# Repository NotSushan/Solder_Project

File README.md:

# CoolPCB

The main function of the PCB is that there is a button which will control the functioning of all the LEDs present in the board. 

## Schematic

## PCB

## How to build
Just order the PCB & components, open up the KiCAD file and build it accordingly.

## BOM
- 1 	Battery
- 4   LED
- 4	  470 Resistor
- 1 	Push Button

Made by Sushan!!

Made as a part of http://solder.hackclub.com/!

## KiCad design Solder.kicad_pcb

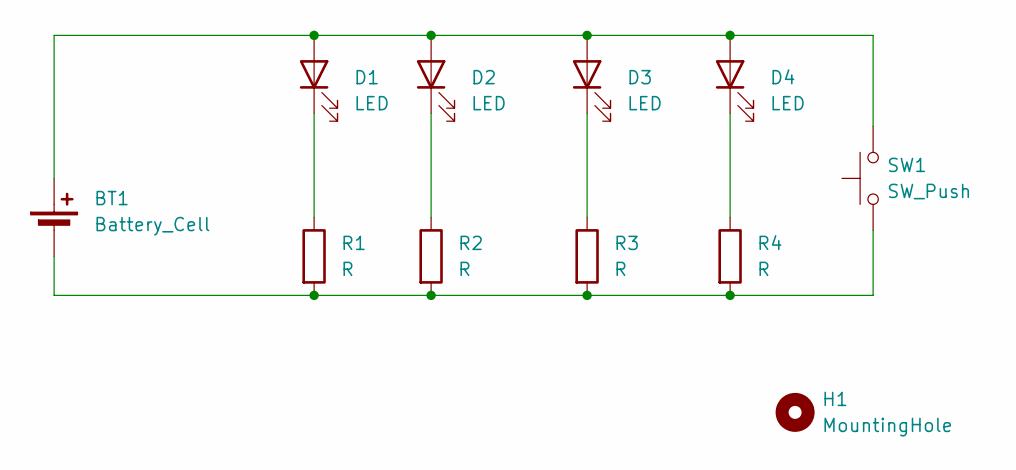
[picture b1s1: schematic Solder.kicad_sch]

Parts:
BT1: Battery_Cell; BatteryHolder_Keystone_3034_1x20mm
D1, D2, D3, D4: LED; LED_D5.0mm
H1: MountingHole; MountingHole_5mm
R1, R2, R3, R4: R; R_Axial_DIN0207_L6.3mm_D2.5mm_P7.62mm_Horizontal
SW1: SW_Push; SW_PUSH_6mm

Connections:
unnamed: BT1.1 (+), D1.2 (A), D2.2 (A), D3.2 (A), D4.2 (A), SW1.2
unnamed: BT1.2 (-), R1.2, R2.2, R3.2, R4.2, SW1.1
unnamed: D1.1 (K), R1.1
unnamed: D2.1 (K), R2.1
unnamed: D3.1 (K), R3.1
unnamed: D4.1 (K), R4.1

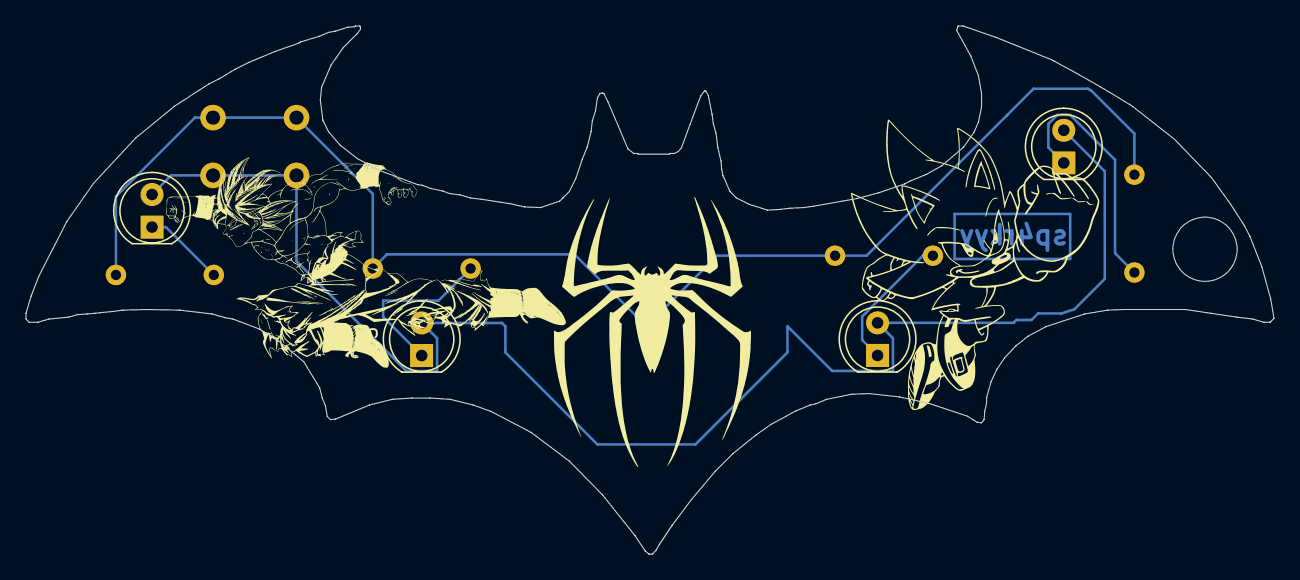
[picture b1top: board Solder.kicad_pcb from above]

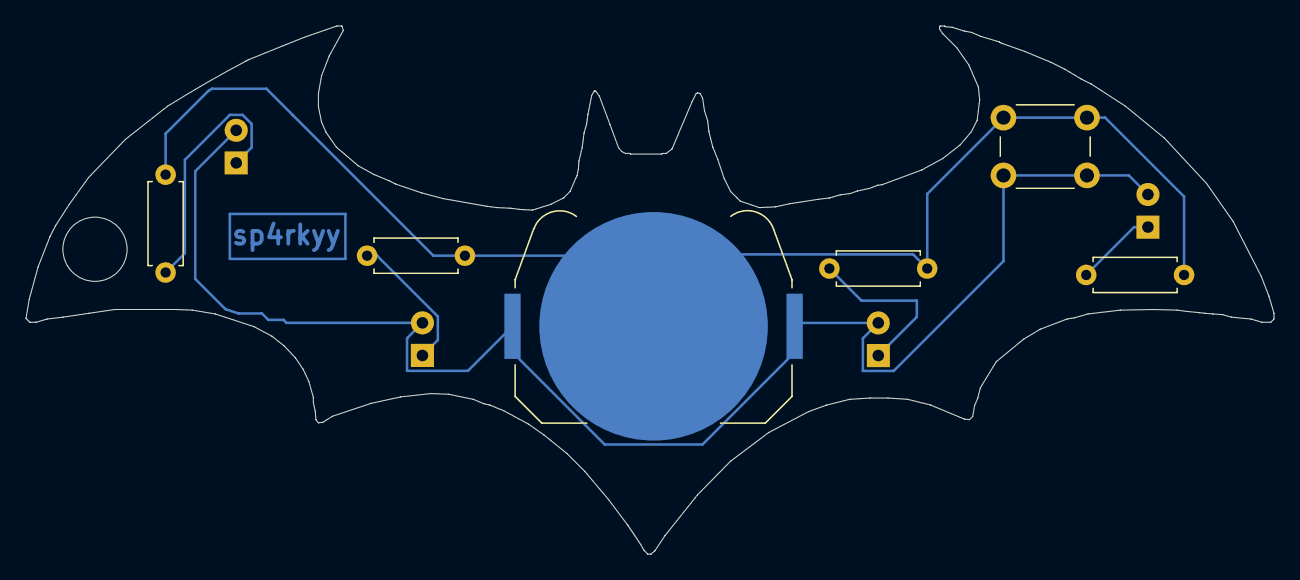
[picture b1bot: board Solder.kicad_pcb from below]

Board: 2 copper layers, 97.2 x 41.1 mm, 11 parts (6 on the bottom side), 6 nets.
